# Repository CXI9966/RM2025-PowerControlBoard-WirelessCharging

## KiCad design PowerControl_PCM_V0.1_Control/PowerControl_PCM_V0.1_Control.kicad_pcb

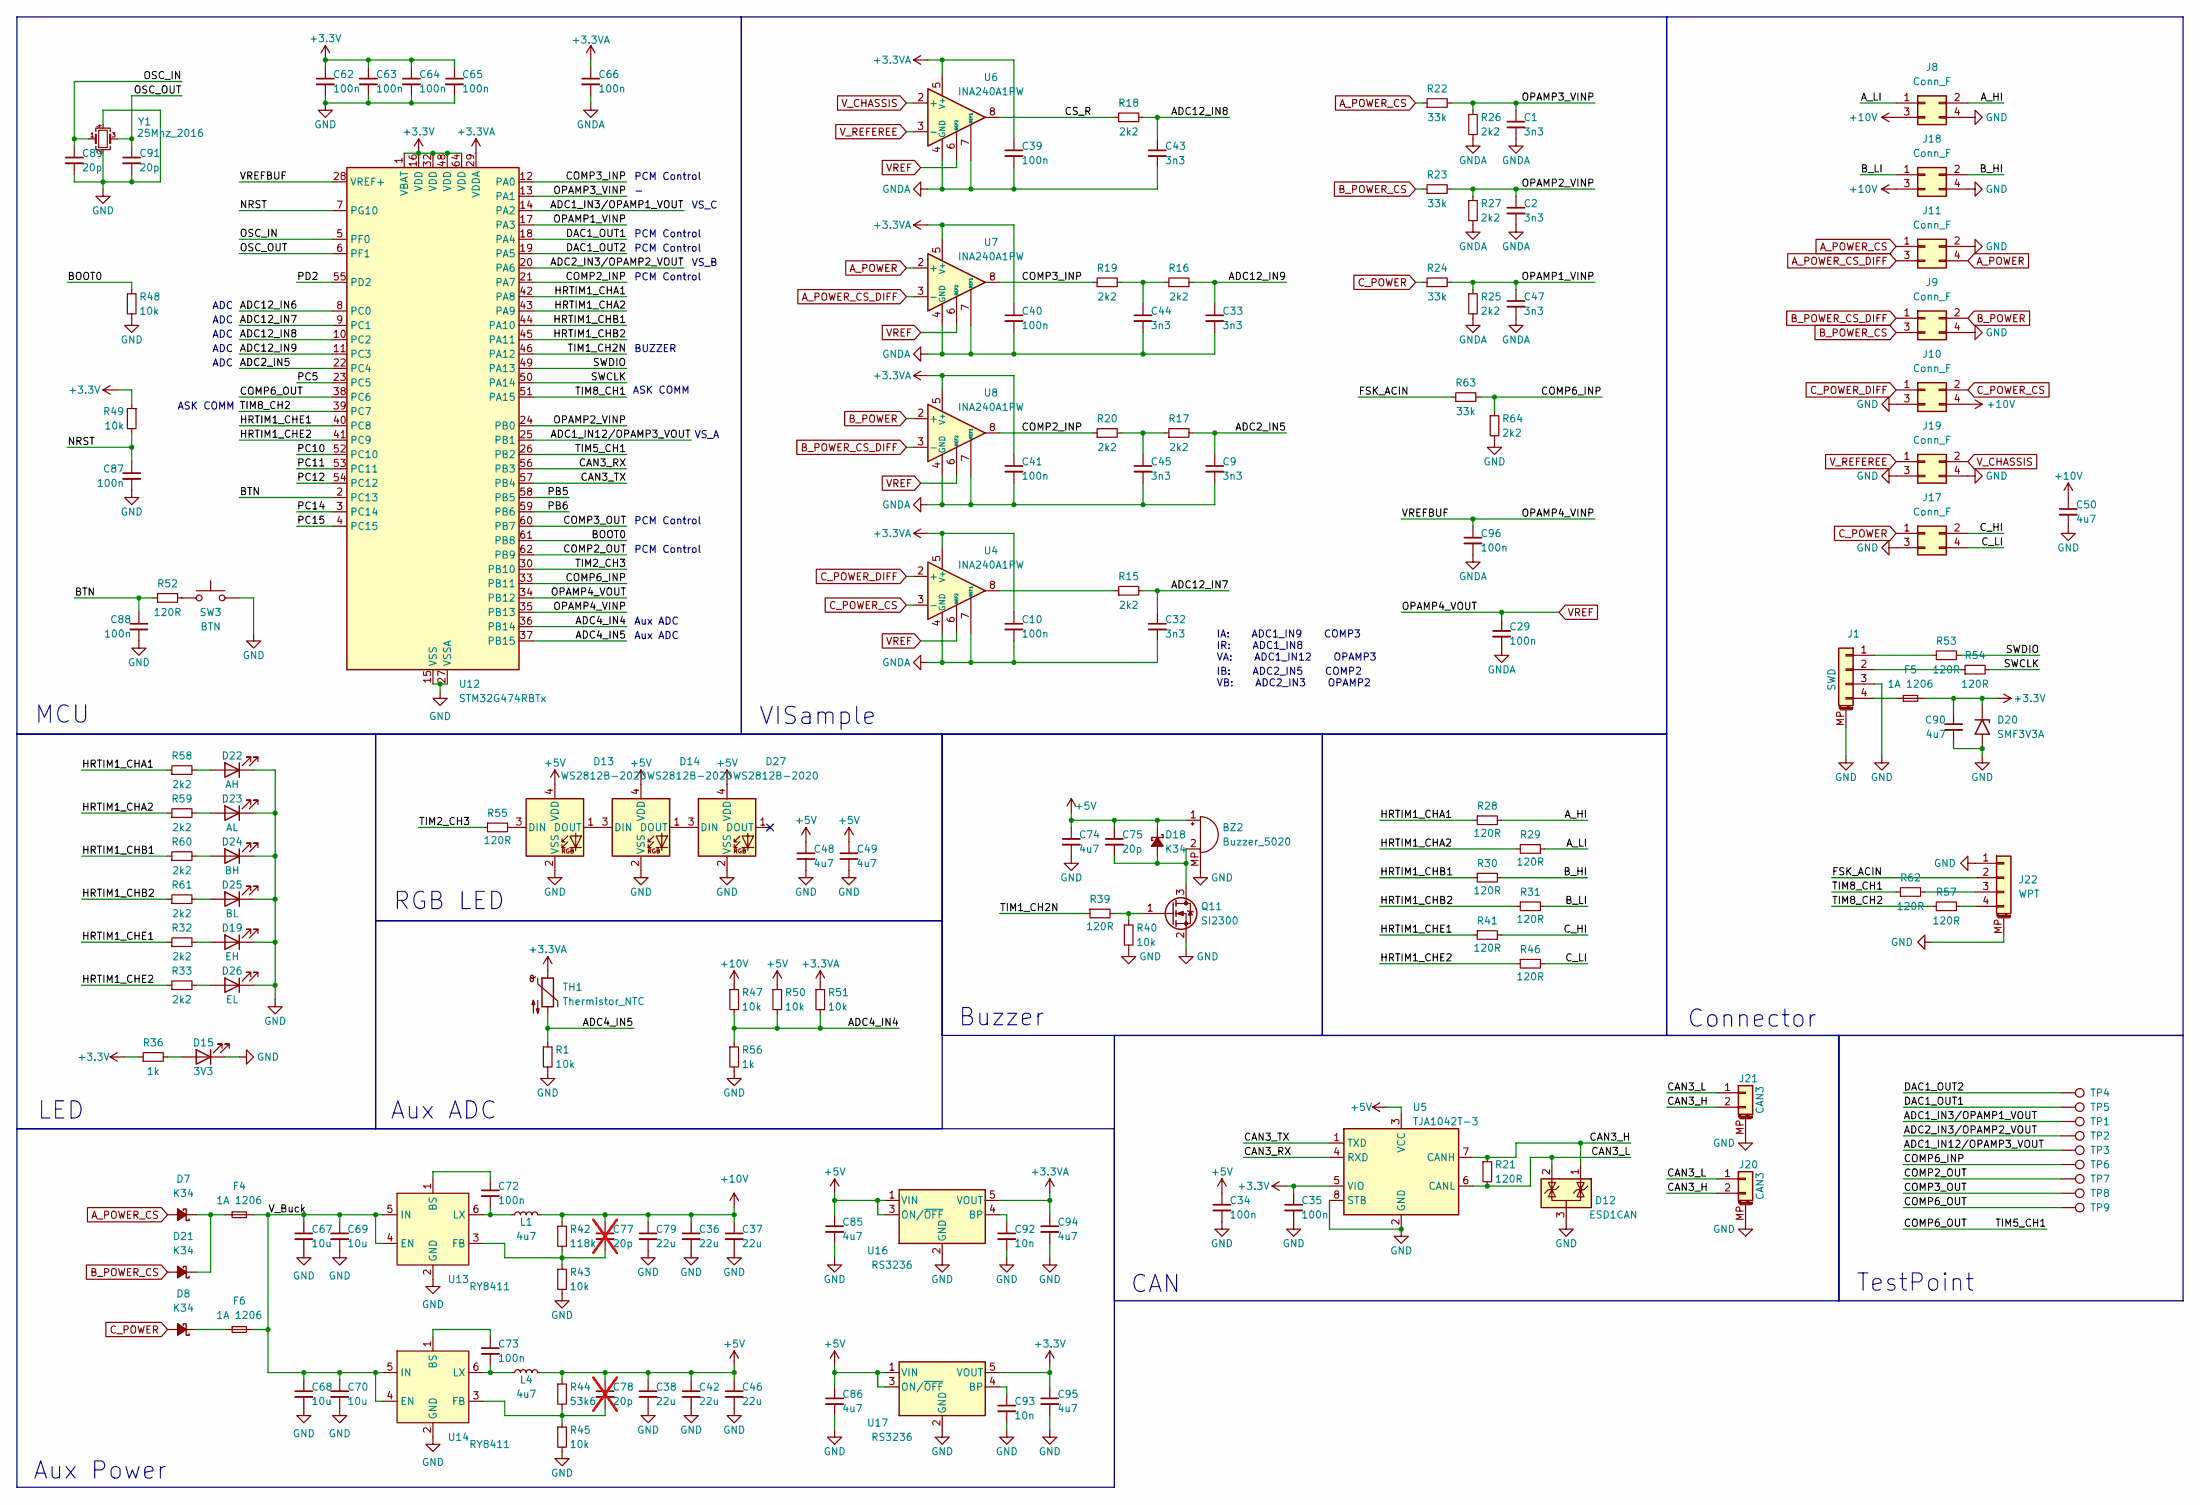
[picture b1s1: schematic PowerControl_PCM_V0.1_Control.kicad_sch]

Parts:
BZ2: Buzzer_5020
C1, C2, C9, C32, C33, C43, C44, C45, C47: 3n3; C_0603_1608Metric
C10, C29, C34, C35, C39, C40, C41, C62, C63, C64, C65, C66, C72, C73, C87, C88, C96: 100n; C_0603_1608Metric
C36, C37, C38, C42, C46, C79: 22u; C_0805_2012Metric
C48, C49, C50, C74, C85, C86, C90, C94, C95: 4u7; C_0603_1608Metric
C67, C68, C69, C70: 10u; C_1206_3216Metric
C75, C89, C91: 20p; C_0603_1608Metric
C77, C78: 20p; C_0603_1608Metric; not fitted
C92, C93: 10n; C_0603_1608Metric
D7, D8, D18, D21: K34; D_SMF
D12: ESD1CAN; SOT-23
D13, D14, D27: WS2812B-2020
D15: 3V3; LED_0603_1608Metric
D19: EH; LED_0603_1608Metric
D20: SMF3V3A; D_SMF
D22: AH; LED_0603_1608Metric
D23: AL; LED_0603_1608Metric
D24: BH; LED_0603_1608Metric
D25: BL; LED_0603_1608Metric
D26: EL; LED_0603_1608Metric
F4, F5, F6: 1A 1206; Fuse_1206_3216Metric
J1: SWD; Molex_PicoBlade_53261-0471_1x04-1MP_P1.25mm_Horizontal
J8, J9, J10, J11, J17, J18, J19: Conn_F; PinSocket_2x02_P2.00mm
J20, J21: CAN3; JST_GH_BM02B-GHS-TBT_1x02-1MP_P1.25mm_Vertical
J22: WPT; JST_GH_BM04B-GHS-TBT_1x04-1MP_P1.25mm_Vertical
L1, L4: 4u7; L_Sunlord_SWPA3015S
Q11: SI2300; SOT-23
R1, R40, R43, R45, R47, R48, R49, R50, R51: 10k; R_0603_1608Metric
R15, R16, R17, R18, R19, R20, R25, R26, R27, R32, R33, R58, R59, R60, R61, R64: 2k2; R_0603_1608Metric
R21, R28, R29, R30, R31, R39, R41, R46, R52, R53, R54, R55, R57, R62: 120R; R_0603_1608Metric
R22, R23, R24, R63: 33k; R_0603_1608Metric
R36, R56: 1k; R_0603_1608Metric
R42: 118k; R_0603_1608Metric
R44: 53k6; R_0603_1608Metric
SW3: BTN; Button_PTS810
TH1: Thermistor_NTC; R_0603_1608Metric
TP1, TP2, TP3, TP4, TP5, TP6, TP7, TP8, TP9: TestPoint; TestPoint_Pad_D1.0mm
U4, U6, U7, U8: INA240A1PW; TSSOP-8_4.4x3mm_P0.65mm
U5: TJA1042T-3; SOIC-8_3.9x4.9mm_P1.27mm
U12: STM32G474RBTx; LQFP-64_10x10mm_P0.5mm
U13, U14: RY8411; SOT-23-6
U16, U17: RS3236; SOT-23-5
Y1: 25Mhz_2016; Crystal_SMD_2016

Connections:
+3.3V: C35.1, C62.1, C63.1, C64.1, C65.1, C90.1, C95.1, D20.1 (A1), F5.2, R36.1, R49.1, U5.5 (VIO), U12.1 (VBAT), U12.16 (VDD), U12.32 (VDD), U12.48 (VDD), U12.64 (VDD), U17.5 (VOUT)
+3.3VA: C10.1, C39.1, C40.1, C41.1, C66.1, C94.1, R51.1, TH1.1, U4.5 (V+), U6.5 (V+), U7.5 (V+), U8.5 (V+), U12.29 (VDDA), U16.5 (VOUT)
+5V: BZ2.1 (+), C34.1, C38.1, C42.1, C46.1, C48.1, C49.1, C74.1, C75.1, C78.1, C85.1, C86.1, D13.4 (VDD), D14.4 (VDD), D18.1 (K), D27.4 (VDD), L4.2, R44.1, R50.1, U5.3 (VCC), U16.1 (VIN), U16.3 (ON/~OFF), U17.1 (VIN), U17.3 (ON/~OFF)
+10V: C36.1, C37.1, C50.1, C77.1, C79.1, J8.3, J10.4, J18.3, L1.2, R42.1, R47.1
/ADC1_IN3/OPAMP1_VOUT: TP1.1, U12.14 (PA2)
/ADC1_IN12/OPAMP3_VOUT: TP3.1, U12.25 (PB1)
/ADC2_IN3/OPAMP2_VOUT: TP2.1, U12.20 (PA6)
/ADC2_IN5: C9.1, R17.2, U12.22 (PC4)
/ADC4_IN4: R47.2, R50.2, R51.2, R56.1, U12.36 (PB14)
/ADC4_IN5: R1.1, TH1.2, U12.37 (PB15)
/ADC12_IN6: U12.8 (PC0)
/ADC12_IN7: C32.1, R15.2, U12.9 (PC1)
/ADC12_IN8: C43.1, R18.2, U12.10 (PC2)
/ADC12_IN9: C33.1, R16.2, U12.11 (PC3)
/A_HI: J8.2, R28.2
/A_LI: J8.1, R29.2
/BOOT0: R48.1, U12.61 (PB8)
/BTN: C88.1, R52.1, U12.2 (PC13)
/B_HI: J18.2, R30.2
/B_LI: J18.1, R31.2
/CAN3_H: D12.1 (K), J20.2, J21.2, R21.1, U5.7 (CANH)
/CAN3_L: D12.2 (K), J20.1, J21.1, R21.2, U5.6 (CANL)
/CAN3_RX: U5.4 (RXD), U12.56 (PB3)
/CAN3_TX: U5.1 (TXD), U12.57 (PB4)
/COMP2_INP: R20.1, U8.8, U12.21 (PA7)
/COMP2_OUT: TP7.1, U12.62 (PB9)
/COMP3_INP: R19.1, U7.8, U12.12 (PA0)
/COMP3_OUT: TP8.1, U12.60 (PB7)
/COMP6_INP: R63.2, R64.1, TP6.1, U12.33 (PB11)
/COMP6_OUT: TP9.1, U12.26 (PB2), U12.38 (PC6)
/CS_R: R18.1, U6.8
/C_HI: J17.2, R41.2
/C_LI: J17.4, R46.2
/DAC1_OUT1: TP5.1, U12.18 (PA4)
/DAC1_OUT2: TP4.1, U12.19 (PA5)
/FSK_ACIN: J22.2, R63.1
/HRTIM1_CHA1: R28.1, R58.1, U12.42 (PA8)
/HRTIM1_CHA2: R29.1, R59.1, U12.43 (PA9)
/HRTIM1_CHB1: R30.1, R60.1, U12.44 (PA10)
/HRTIM1_CHB2: R31.1, R61.1, U12.45 (PA11)
/HRTIM1_CHE1: R32.1, R41.1, U12.40 (PC8)
/HRTIM1_CHE2: R33.1, R46.1, U12.41 (PC9)
/NRST: C87.1, R49.2, U12.7 (PG10)
/OPAMP1_VINP: C47.1, R24.2, R25.1, U12.17 (PA3)
/OPAMP2_VINP: C2.1, R23.2, R27.1, U12.24 (PB0)
/OPAMP3_VINP: C1.1, R22.2, R26.1, U12.13 (PA1)
/OPAMP4_VINP: C96.1, U12.28 (VREF+), U12.35 (PB13)
/OSC_IN: C89.1, U12.5 (PF0), Y1.1
/OSC_OUT: C91.1, U12.6 (PF1), Y1.3
/PB5: U12.58 (PB5)
/PB6: U12.59 (PB6)
/PC5: U12.23 (PC5)
/PC10: U12.52 (PC10)
/PC11: U12.53 (PC11)
/PC12: U12.54 (PC12)
/PC14: U12.3 (PC14)
/PC15: U12.4 (PC15)
/PD2: U12.55 (PD2)
/SWCLK: R54.2, U12.50 (PA14)
/SWDIO: R53.2, U12.49 (PA13)
/TIM1_CH2N: R39.1, U12.46 (PA12)
/TIM2_CH3: R55.1, U12.30 (PB10)
/TIM8_CH1: R62.1, U12.51 (PA15)
/TIM8_CH2: R57.1, U12.39 (PC7)
/V_Buck: C67.1, C68.1, C69.1, C70.1, F4.2, F6.2, U13.4 (EN), U13.5 (IN), U14.4 (EN), U14.5 (IN)
A_POWER: J11.4, U7.2 (+)
A_POWER_CS: D7.2 (A), J11.1, R22.1
A_POWER_CS_DIFF: J11.3, U7.3 (-)
B_POWER: J9.2, U8.2 (+)
B_POWER_CS: D21.2 (A), J9.3, R23.1
B_POWER_CS_DIFF: J9.1, U8.3 (-)
C_POWER: D8.2 (A), J17.1, R24.1
C_POWER_CS: J10.2, U4.3 (-)
C_POWER_DIFF: J10.1, U4.2 (+)
GND: BZ2.MP, C34.2, C35.2, C36.2, C37.2, C38.2, C42.2, C46.2, C48.2, C49.2, C50.2, C62.2, C63.2, C64.2, C65.2, C67.2, C68.2, C69.2, C70.2, C74.2, C79.2, C85.2, C86.2, C87.2, C88.2, C89.2, C90.2, C91.2, C92.2, C93.2, C94.2, C95.2, D12.3 (A), D13.2 (VSS), D14.2 (VSS), D15.1 (K), D19.1 (K), D20.2 (A2), D22.1 (K), D23.1 (K), D24.1 (K), D25.1 (K), D26.1 (K), D27.2 (VSS), J1.3, J1.MP (MountPin), J8.4, J9.4, J10.3, J11.2, J17.3, J18.4, J19.3, J19.4, J20.MP (MountPin), J21.MP (MountPin), J22.1, J22.MP (MountPin), Q11.2 (S), R1.2, R40.2, R43.2, R45.2, R48.2, R56.2, R64.2, SW3.2, U5.2 (GND), U5.8 (STB), U12.15 (VSS), U12.27 (VSSA), U12.31 (VSS), U12.47 (VSS), U12.63 (VSS), U13.2 (GND), U14.2 (GND), U16.2 (GND), U17.2 (GND), Y1.2, Y1.4
GNDA: C1.2, C2.2, C9.2, C10.2, C29.2, C32.2, C33.2, C39.2, C40.2, C41.2, C43.2, C44.2, C45.2, C47.2, C66.2, C96.2, R25.2, R26.2, R27.2, U4.1 (GND), U4.4 (GND), U4.7 (REF1), U6.1 (GND), U6.4 (GND), U6.7 (REF1), U7.1 (GND), U7.4 (GND), U7.7 (REF1), U8.1 (GND), U8.4 (GND), U8.7 (REF1)
unnamed: BZ2.2 (-), C75.2, D18.2 (A), Q11.3 (D)
unnamed: C44.1, R16.1, R19.2
unnamed: C45.1, R17.1, R20.2
unnamed: D8.1 (K), F6.1
unnamed: D13.3 (DIN), R55.2
unnamed: D13.1 (DOUT), D14.3 (DIN)
unnamed: D14.1 (DOUT), D27.3 (DIN)
unnamed: D15.2 (A), R36.2
unnamed: D19.2 (A), R32.2
unnamed: D7.1 (K), D21.1 (K), F4.1
unnamed: D22.2 (A), R58.2
unnamed: D23.2 (A), R59.2
unnamed: D24.2 (A), R60.2
unnamed: D25.2 (A), R61.2
unnamed: D26.2 (A), R33.2
unnamed: J1.1, R53.1
unnamed: J1.2, R54.1
unnamed: F5.1, J1.4
unnamed: J22.3, R62.2
unnamed: J22.4, R57.2
unnamed: Q11.1 (G), R39.2, R40.1
unnamed: R15.1, U4.8
unnamed: R52.2, SW3.1
unnamed: C72.1, U13.1 (BS)
unnamed: C77.2, R42.2, R43.1, U13.3 (FB)
unnamed: C72.2, L1.1, U13.6 (LX)
unnamed: C73.1, U14.1 (BS)
unnamed: C78.2, R44.2, R45.1, U14.3 (FB)
unnamed: C73.2, L4.1, U14.6 (LX)
unnamed: C92.1, U16.4 (BP)
unnamed: C93.1, U17.4 (BP)
VREF: C29.1, U4.6 (REF2), U6.6 (REF2), U7.6 (REF2), U8.6 (REF2), U12.34 (PB12)
V_CHASSIS: J19.2, U6.2 (+)
V_REFEREE: J19.1, U6.3 (-)

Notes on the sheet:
Aux ADC
VS_A
ADC
IA: ADC1_IN9 COMP3 IR: ADC1_IN8 VA: ADC1_IN12 OPAMP3
PCM Control
Buzzer
TestPoint
CAN
Connector
VS_C
BUZZER
VISample
IB: ADC2_IN5 COMP2 VB: ADC2_IN3 OPAMP2
ASK COMM
LED
RGB LED
Aux Power
VS_B
MCU

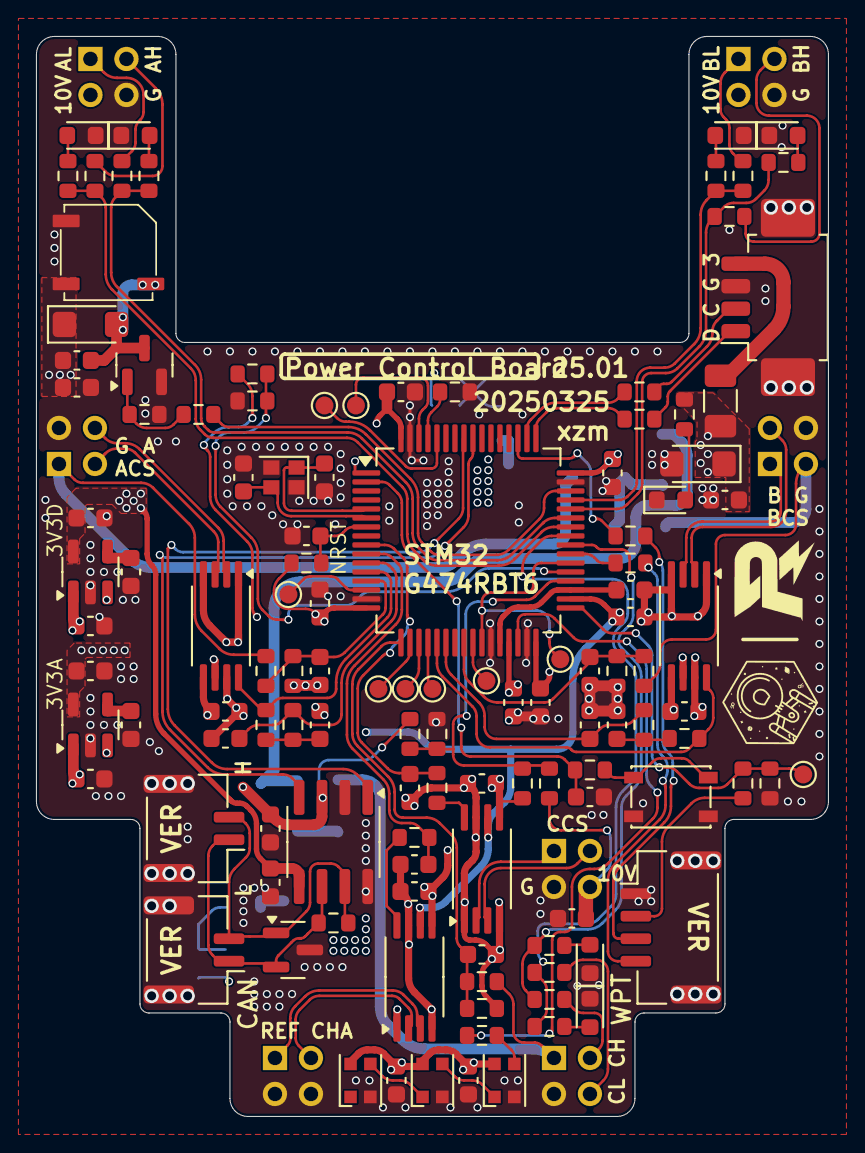
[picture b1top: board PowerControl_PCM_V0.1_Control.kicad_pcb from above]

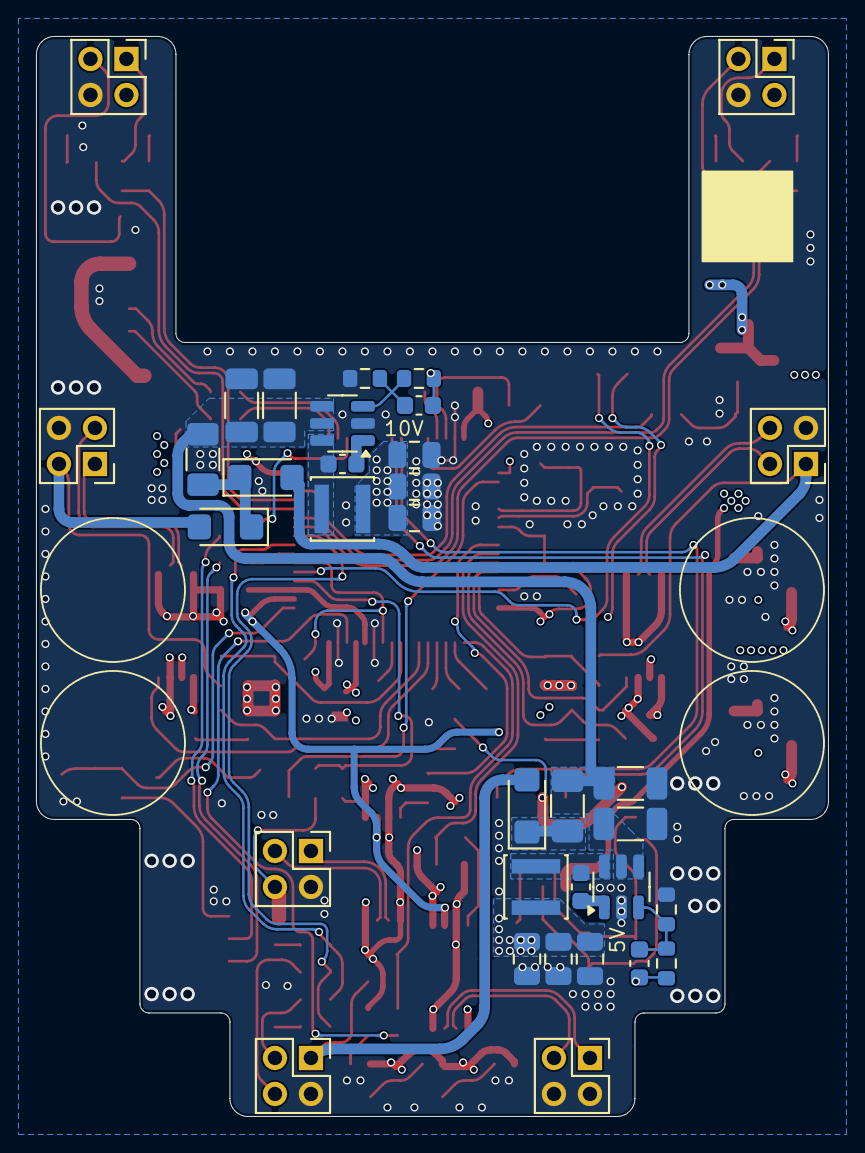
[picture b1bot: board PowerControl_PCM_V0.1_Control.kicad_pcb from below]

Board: 4 copper layers, 44.0 x 60.0 mm, 155 parts (34 on the bottom side), 100 nets.

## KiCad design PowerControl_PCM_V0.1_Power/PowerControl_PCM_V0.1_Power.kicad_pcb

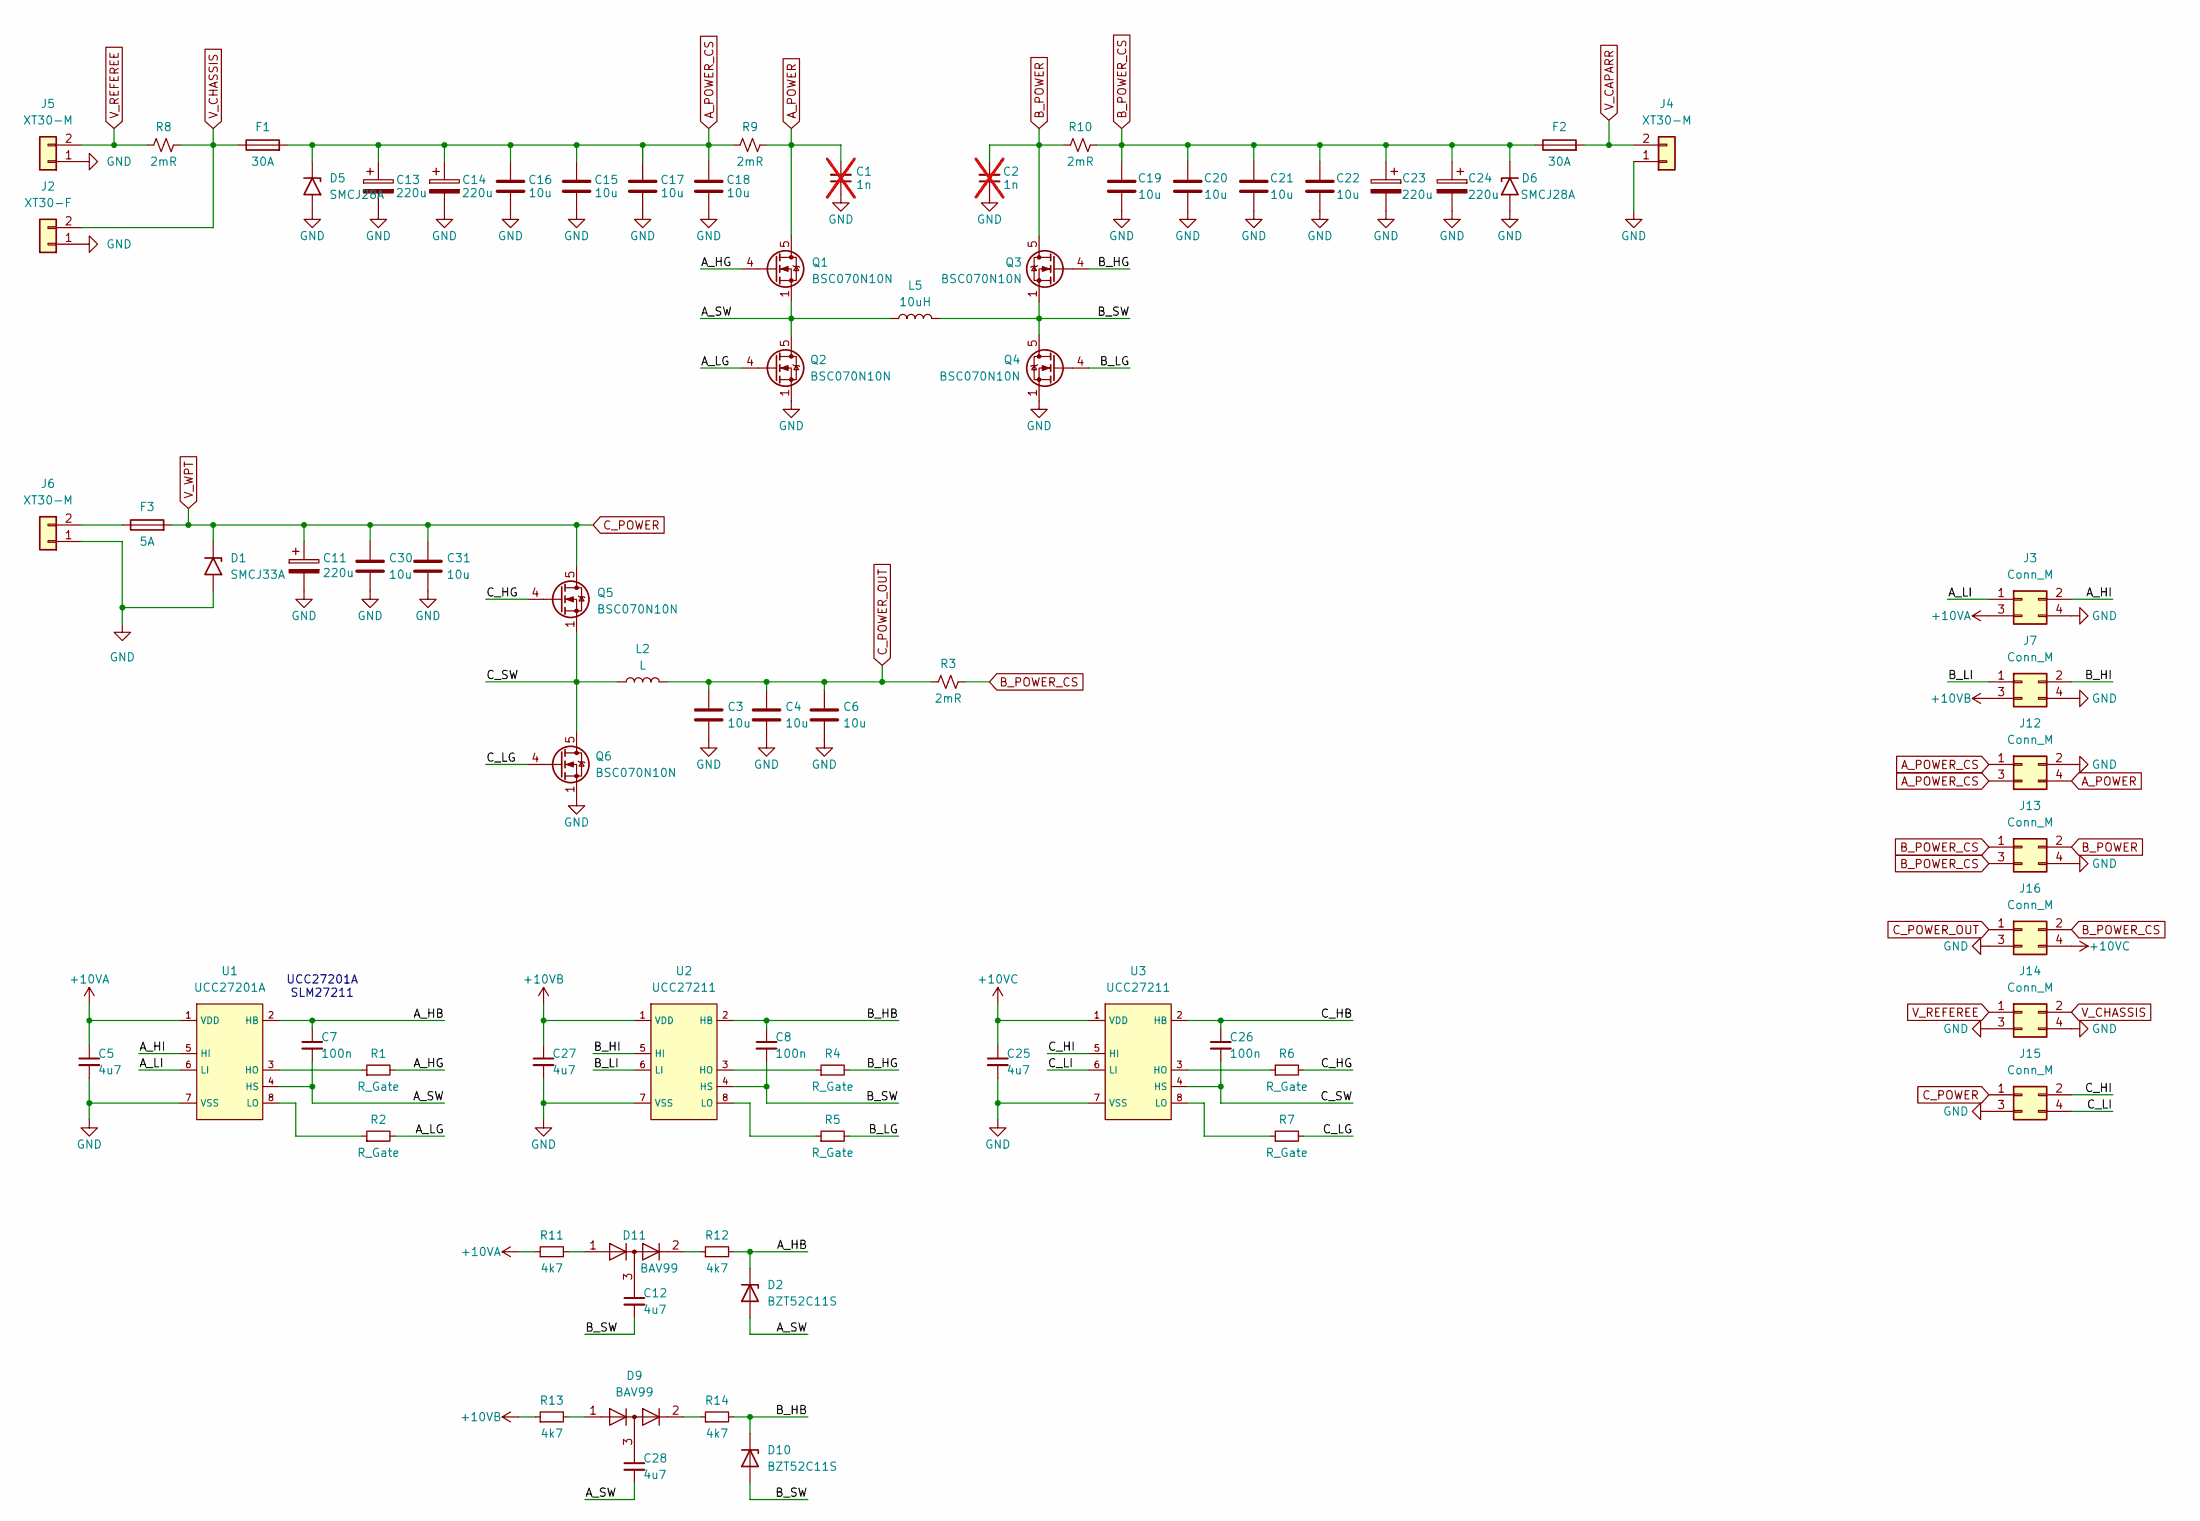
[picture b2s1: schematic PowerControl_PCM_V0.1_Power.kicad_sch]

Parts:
C1, C2: 1n; C_0603_1608Metric; not fitted
C3, C4, C6, C15, C16, C17, C18, C19, C20, C21, C22, C30, C31: 10u; C_1206_3216Metric
C5, C12, C25, C27, C28: 4u7; C_0603_1608Metric
C7, C8, C26: 100n; C_0603_1608Metric
C11, C13, C14, C23, C24: 220u; C_D8.0mm_P3.50mm
D1: SMCJ33A; D_SMC
D2, D10: BZT52C11S; D_SOD-323_HandSoldering
D5, D6: SMCJ28A; D_SMC
D9, D11: BAV99; SOT-23
F1, F2: 30A; Fuse_Littelfuse-NANO2-451_453
F3: 5A; Fuse_Littelfuse-NANO2-451_453
J2: XT30-F; AMASS_XT30U-F_1x02_P5.0mm_Vertical
J3, J7, J12, J13, J14, J15, J16: Conn_M; PinHeader_2x02_P2.00mm_Vertical_SMD
J4, J5, J6: XT30-M; AMASS_XT30U-M_1x02_P5.0mm_Vertical
L2: L; L_Wuerth_HCI-1040
L5: 10uH; L_VER2923
Q1, Q2, Q3, Q4, Q5, Q6: BSC070N10N; TDSON-8-1
R1, R2, R4, R5, R6, R7: R_Gate; R_0603_1608Metric
R3, R8, R9, R10: 2mR; R_2512_6332Metric
R11, R12, R13, R14: 4k7; R_0603_1608Metric
U1: UCC27201A; SOIC-8_3.9x4.9mm_P1.27mm
U2, U3: UCC27211; SOIC-8_3.9x4.9mm_P1.27mm

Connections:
+10VA: C5.1, J3.3, R11.1, U1.1 (VDD)
+10VB: C27.1, J7.3, R13.1, U2.1 (VDD)
+10VC: C25.1, J16.4, U3.1 (VDD)
/A_HB: C7.1, D2.1 (K), R12.2, U1.2 (HB)
/A_HG: Q1.4 (G), R1.2
/A_HI: J3.2, U1.5 (HI)
/A_LG: Q2.4 (G), R2.2
/A_LI: J3.1, U1.6 (LI)
/A_SW: C7.2, C28.2, D2.2 (A), L5.1, Q1.1 (S), Q1.2 (S), Q1.3 (S), Q2.5 (D), U1.4 (HS)
/B_HB: C8.1, D10.1 (K), R14.2, U2.2 (HB)
/B_HG: Q3.4 (G), R4.2
/B_HI: J7.2, U2.5 (HI)
/B_LG: Q4.4 (G), R5.2
/B_LI: J7.1, U2.6 (LI)
/B_SW: C8.2, C12.2, D10.2 (A), L5.2, Q3.1 (S), Q3.2 (S), Q3.3 (S), Q4.5 (D), U2.4 (HS)
/C_HB: C26.1, U3.2 (HB)
/C_HG: Q5.4 (G), R6.2
/C_HI: J15.2, U3.5 (HI)
/C_LG: Q6.4 (G), R7.2
/C_LI: J15.4, U3.6 (LI)
/C_SW: C26.2, L2.1, Q5.1 (S), Q5.2 (S), Q5.3 (S), Q6.5 (D), U3.4 (HS)
A_POWER: C1.2, J12.4, Q1.5 (D), R9.2
A_POWER_CS: C13.1, C14.1, C15.2, C16.2, C17.2, C18.2, D5.1 (A1), F1.2, J12.1, J12.3, R9.1
B_POWER: C2.2, J13.2, Q3.5 (D), R10.1
B_POWER_CS: C19.2, C20.2, C21.2, C22.2, C23.1, C24.1, D6.1 (A1), F2.1, J13.1, J13.3, J16.2, R3.2, R10.2
C_POWER: C11.1, C30.1, C31.1, D1.1 (A1), F3.2, J15.1, Q5.5 (D)
C_POWER_OUT: C3.1, C4.1, C6.1, J16.1, L2.2, R3.1
GND: C1.1, C2.1, C3.2, C4.2, C5.2, C6.2, C11.2, C13.2, C14.2, C15.1, C16.1, C17.1, C18.1, C19.1, C20.1, C21.1, C22.1, C23.2, C24.2, C25.2, C27.2, C30.2, C31.2, D1.2 (A2), D5.2 (A2), D6.2 (A2), J2.1, J3.4, J4.1, J5.1, J6.1, J7.4, J12.2, J13.4, J14.3, J14.4, J15.3, J16.3, Q2.1 (S), Q2.2 (S), Q2.3 (S), Q4.1 (S), Q4.2 (S), Q4.3 (S), Q6.1 (S), Q6.2 (S), Q6.3 (S), U1.7 (VSS), U2.7 (VSS), U3.7 (VSS)
unnamed: C12.1, D11.3 (K)
unnamed: C28.1, D9.3 (K)
unnamed: D9.2 (A), R14.1
unnamed: D9.1 (K), R13.2
unnamed: D11.2 (A), R12.1
unnamed: D11.1 (K), R11.2
unnamed: F3.1, J6.2
unnamed: R1.1, U1.3 (HO)
unnamed: R2.1, U1.8 (LO)
unnamed: R4.1, U2.3 (HO)
unnamed: R5.1, U2.8 (LO)
unnamed: R6.1, U3.3 (HO)
unnamed: R7.1, U3.8 (LO)
V_CAPARR: F2.2, J4.2
V_CHASSIS: F1.1, J2.2, J14.2, R8.2
V_REFEREE: J5.2, J14.1, R8.1

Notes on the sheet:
UCC27201A SLM27211

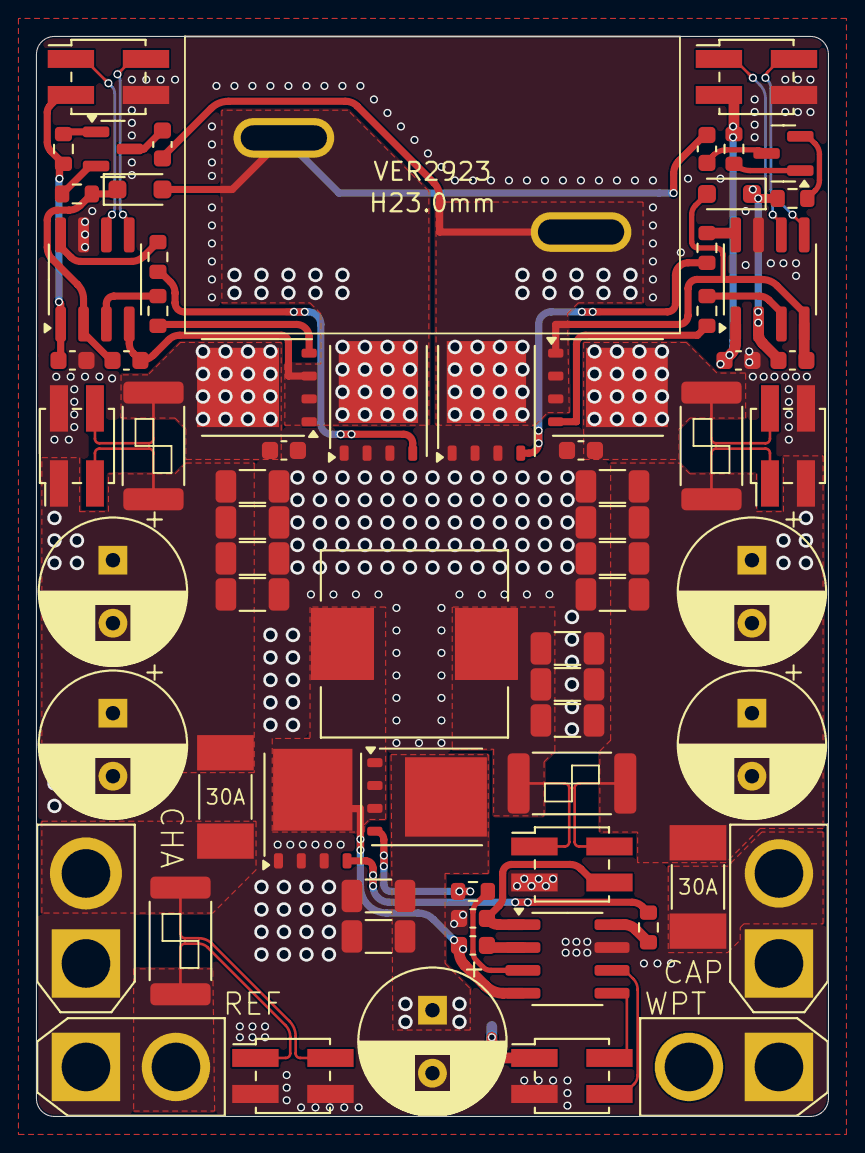
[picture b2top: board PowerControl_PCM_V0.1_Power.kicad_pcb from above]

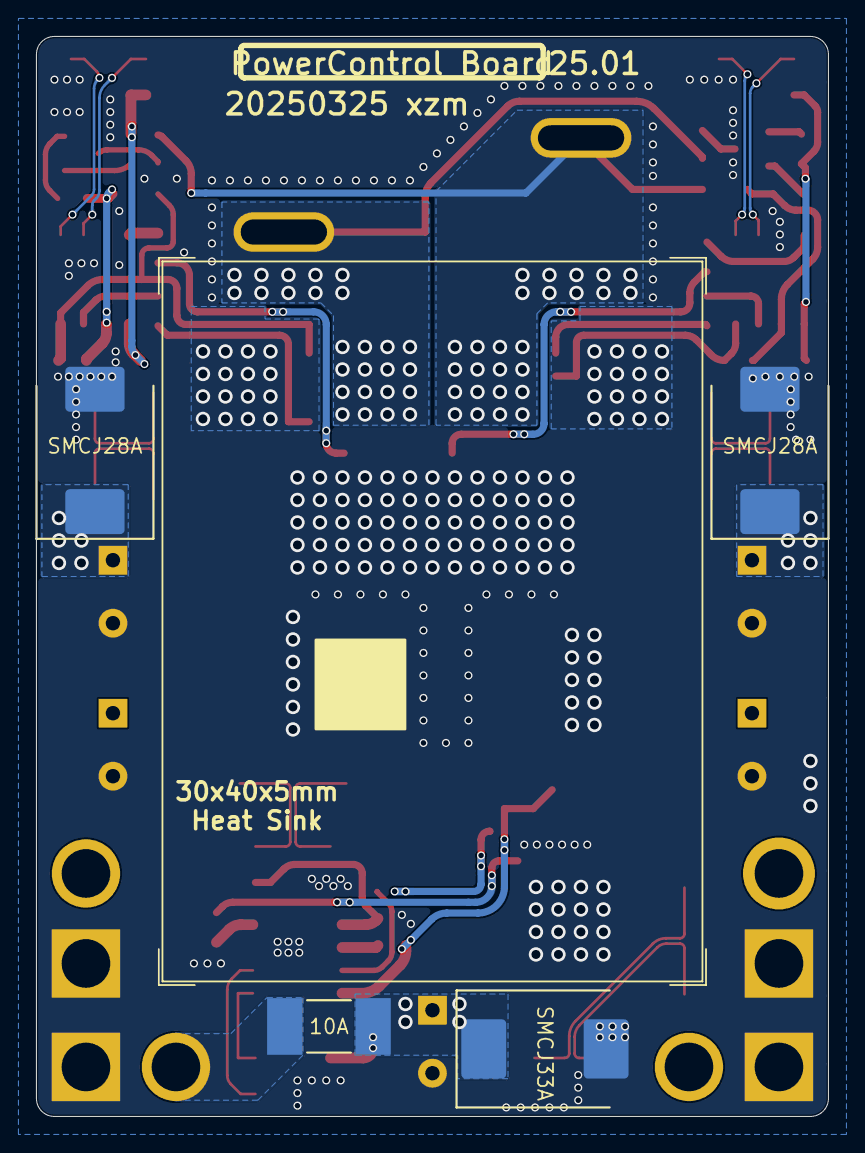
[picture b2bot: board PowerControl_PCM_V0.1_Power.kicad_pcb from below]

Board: 2 copper layers, 44.0 x 60.0 mm, 74 parts (4 on the bottom side), 44 nets.
